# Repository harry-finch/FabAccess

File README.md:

# FabAccess
An RFID control panel to access machines in a fablab.

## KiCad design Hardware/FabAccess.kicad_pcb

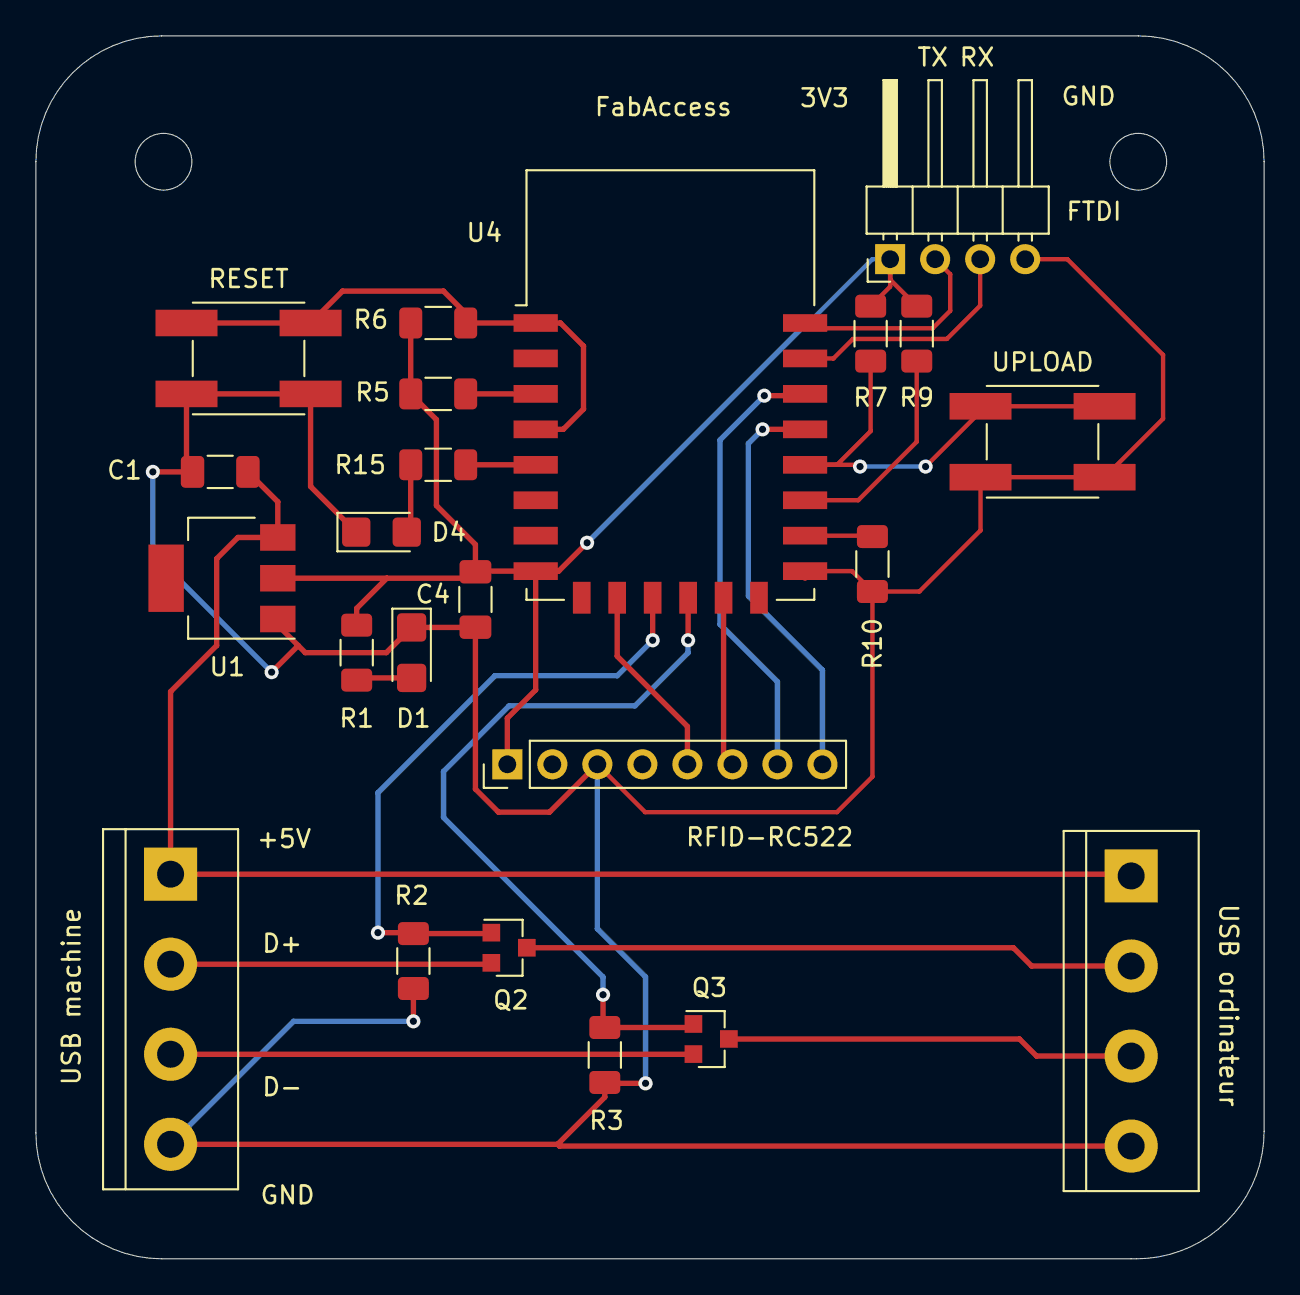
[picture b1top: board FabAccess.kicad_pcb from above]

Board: 2 copper layers, 69.3 x 69.0 mm, 23 parts (0 on the bottom side), 23 nets.

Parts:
C1, C4: 1u; C_1206_3216Metric_Pad1.33x1.80mm_HandSolder
D1, D4: LED; LED_1206_3216Metric_Castellated
FTDI: Conn_01x04; PinHeader_1x04_P2.54mm_Horizontal
J2: USB_computer; TerminalBlock_bornier-4_P5.08mm
J3: USB_machine; TerminalBlock_bornier-4_P5.08mm
J4: RFID-RC522; PinHeader_1x08_P2.54mm_Vertical
Q2, Q3: MOSFET_N-CH_30V_1.7A; SOT-23
R1, R15: 470; R_1206_3216Metric_Pad1.30x1.75mm_HandSolder
R2, R3, R5, R6, R7, R9, R10: 10K; R_1206_3216Metric_Pad1.30x1.75mm_HandSolder
RESET: BUTTON_B3SN; Button_Omron_B3SN_6x6mm
U1: LM1117-3.3; SOT-223
U4: ESP-12E
UPLOAD: BUTTON_B3SN; Button_Omron_B3SN_6x6mm

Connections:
+3V3: C4.1, FTDI.1, J4.1, R1.2, R5.1, R6.1, R7.1, R9.1, U1.2, U4.8
+5V: C1.1, J2.1, J3.1, U1.3
D+_CTRL: Q2.1, R2.1, U4.11
D+_computer: J2.2, Q2.3
D+_machine: J3.2, Q2.2
D-_CTRL: Q3.1, R3.1, U4.12
D-_computer: J2.3, Q3.3
D-_machine: J3.3, Q3.2
GND: C1.2, C4.2, D1.1, D4.1, FTDI.4, J2.4, J3.4, J4.3, R2.2, R3.2, R10.2, RESET.2, U1.1, U4.15, UPLOAD.2
IO0: R7.2, U4.18, UPLOAD.1
LED: R15.2, U4.5
MISO: J4.5, U4.10
MOSI: J4.6, U4.13
unnamed: D1.2, R1.1
unnamed: D4.2, R15.1
unnamed: R5.2, U4.3
unnamed: R9.2, U4.17
unnamed: R10.1, U4.16
RESET: R6.2, RESET.1, U4.1, U4.4
RX: FTDI.3, U4.21
SCL: J4.7, U4.20
SDA: J4.8, U4.19
TX: FTDI.2, U4.22

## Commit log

2021-04-30 Directories
2021-04-30 KiCAD files
2021-04-30 rm DS_Store
2021-04-30 KiCAD project
